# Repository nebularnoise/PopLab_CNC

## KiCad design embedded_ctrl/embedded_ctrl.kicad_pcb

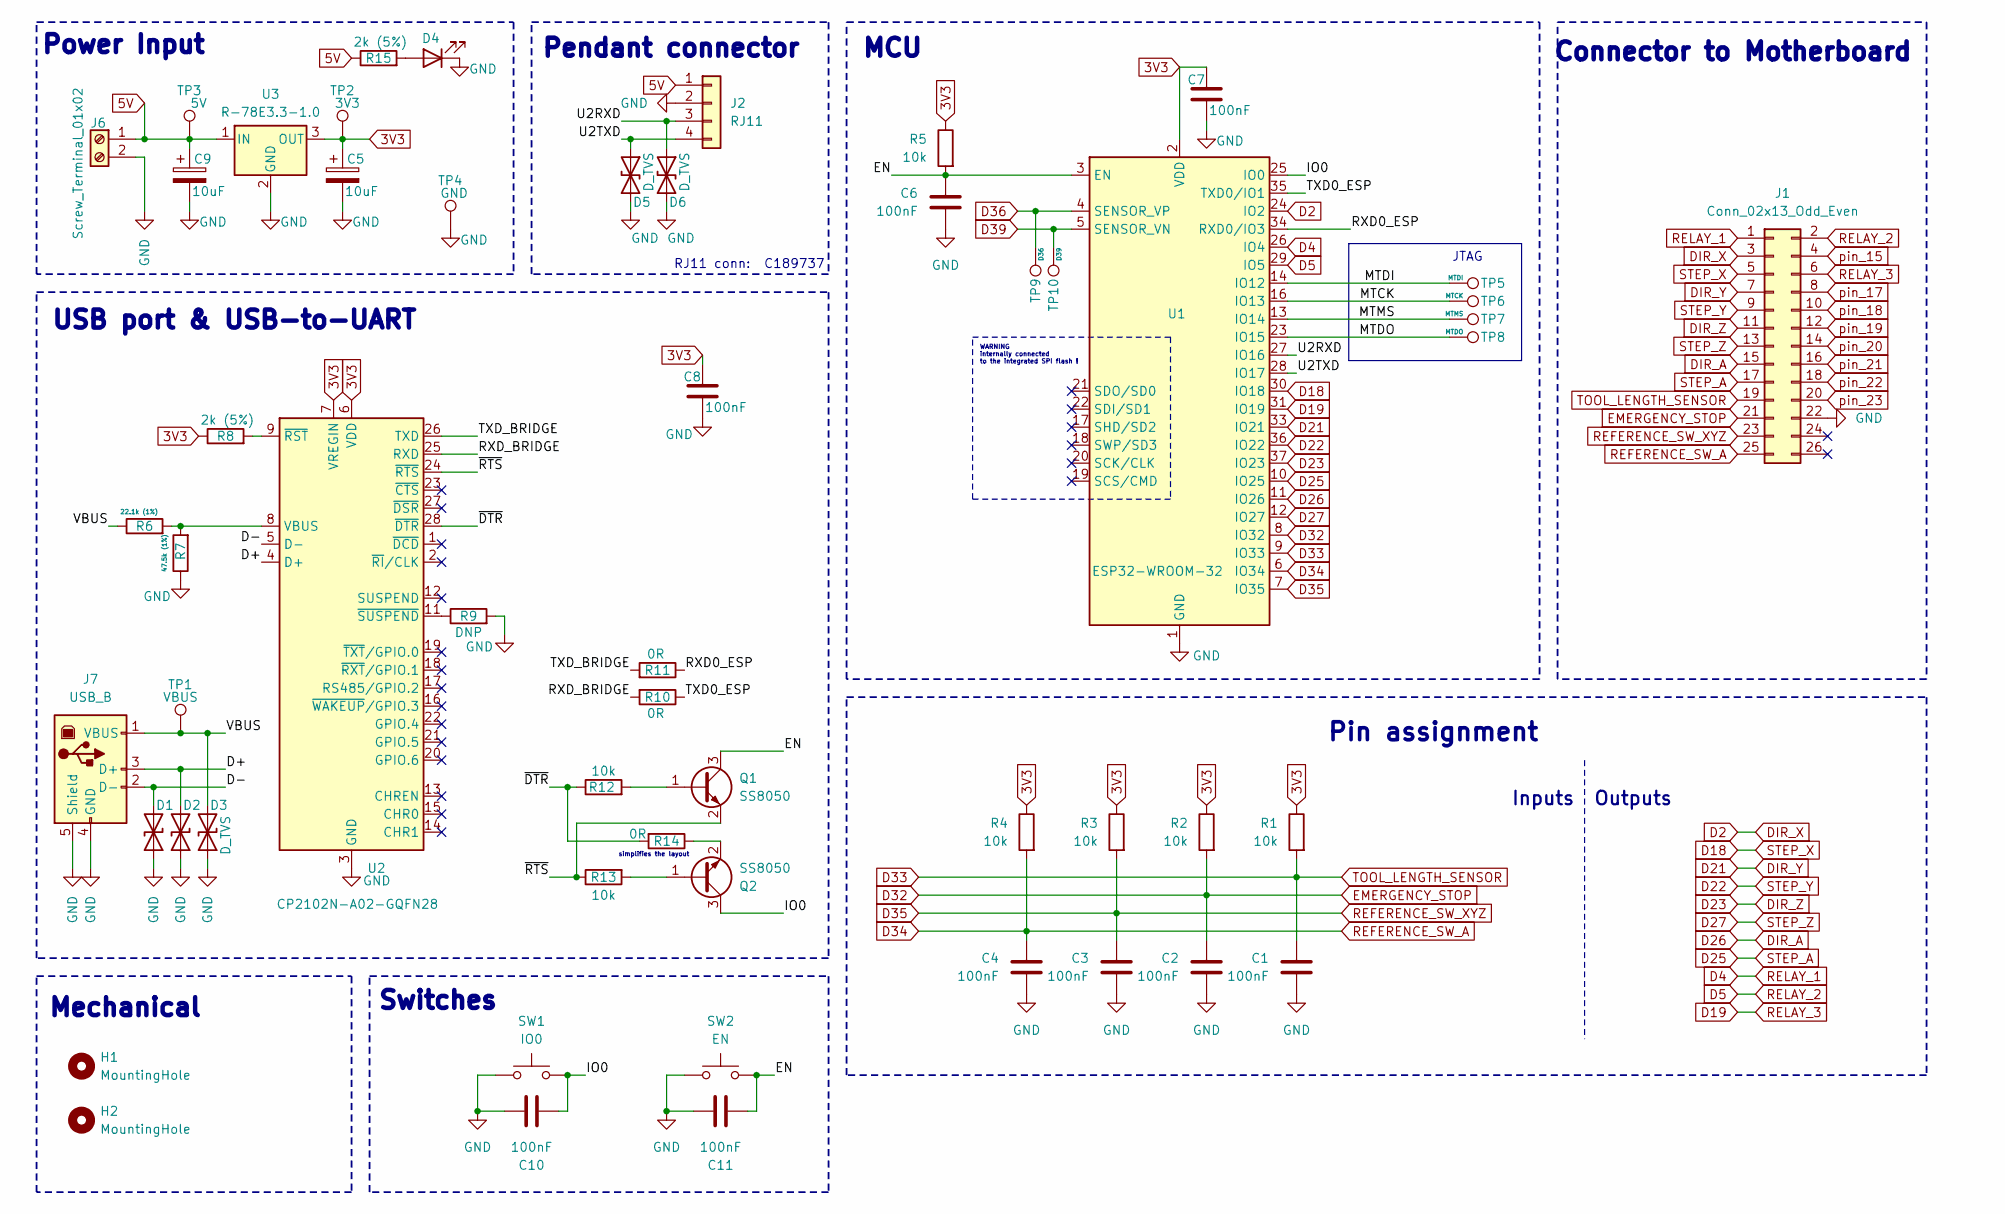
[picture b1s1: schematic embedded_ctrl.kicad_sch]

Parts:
C1, C2, C3, C4, C6, C7, C8, C10, C11: 100nF; C_0603_1608Metric; JLCPCB Part # C14663
C5, C9: 10uF; CP_Elec_5x5.4; JLCPCB Part # C72487
D1, D2, D3, D5, D6: D_TVS; D_0603_1608Metric; JLCPCB Part # C316054
D4: LED; D_0603_1608Metric; JLCPCB Part # C2286
H1, H2: MountingHole; MountingHole_3.2mm_M3
J1: Conn_02x13_Odd_Even; PinHeader_2x13_P2.54mm_Horizontal; JLCPCB Part # C2894993
J2: RJ11; RJ11_C189737
J6: Screw_Terminal_01x02; TerminalBlock_Phoenix_MKDS-1,5-2_1x02_P5.00mm_Horizontal; JLCPCB Part # C8465
J7: USB_B; USB_B_OST_USB-B1HSxx_Horizontal; JLCPCB Part # C720549
Q1, Q2: SS8050; SOT-23; JLCPCB Part # C2150
R1, R2, R3, R4, R5, R12, R13: 10k; R_0603_1608Metric; JLCPCB Part # C25804
R6: 22.1k (1%); R_0603_1608Metric; JLCPCB Part # C25961
R7: 47.5k (1%); R_0603_1608Metric; JLCPCB Part # C25961
R8, R15: 2k (5%); R_0603_1608Metric; JLCPCB Part # C22975
R9: DNP; R_0603_1608Metric
R10, R11, R14: 0R; R_0603_1608Metric; JLCPCB Part # C21189
SW1: IO0; SW_Push_1P1T_NO_Vertical_Wuerth_434133025816
SW2: EN; SW_Push_1P1T_NO_Vertical_Wuerth_434133025816
TP1: VBUS; TestPoint_THTPad_D1.0mm_Drill0.5mm
TP2: 3V3; TestPoint_THTPad_D1.0mm_Drill0.5mm
TP3: 5V; TestPoint_THTPad_D1.0mm_Drill0.5mm
TP4: GND; TestPoint_THTPad_D1.0mm_Drill0.5mm
TP5: MTDI; TestPoint_Pad_D1.0mm
TP6: MTCK; TestPoint_Pad_D1.0mm
TP7: MTMS; TestPoint_Pad_D1.0mm
TP8: MTDO; TestPoint_Pad_D1.0mm
TP9: D36; TestPoint_Pad_D1.0mm
TP10: D39; TestPoint_Pad_D1.0mm
U1: ESP32-WROOM-32
U2: CP2102N-A02-GQFN28; QFN-28-1EP_5x5mm_P0.5mm_EP3.35x3.35mm; JLCPCB Part # C964632
U3: R-78E3.3-1.0; Converter_DCDC_RECOM_R-78E-0.5_THT; JLCPCB Part # C18212316

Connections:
3V3: C5.1, C7.1, C8.1, R1.1, R2.1, R3.1, R4.1, R5.1, R8.1, TP2.1, U1.2 (VDD), U2.6 (VDD), U2.7 (VREGIN), U3.3 (OUT)
5V: C9.1, J2.1, J6.1, R15.1, TP3.1, U3.1 (IN)
/D+: D2.2 (A2), J7.3 (D+), U2.4 (D+)
/D-: D1.2 (A2), J7.2 (D-), U2.5 (D-)
/EN: C6.1, C11.1, Q1.3 (C), R5.2, SW2.2, U1.3 (EN)
/IO0: C10.1, Q2.3 (C), SW1.2, U1.25 (IO0)
/MTCK: TP6.1, U1.16 (IO13)
/MTDI: TP5.1, U1.14 (IO12)
/MTDO: TP8.1, U1.23 (IO15)
/MTMS: TP7.1, U1.13 (IO14)
/RXD0_ESP: R11.1, U1.34 (RXD0/IO3)
/RXD_BRIDGE: R10.2, U2.25 (RXD)
/TXD0_ESP: R10.1, U1.35 (TXD0/IO1)
/TXD_BRIDGE: R11.2, U2.26 (TXD)
/U2RXD: D6.1 (A1), J2.3, U1.27 (IO16)
/U2TXD: D5.1 (A1), J2.4, U1.28 (IO17)
/VBUS: D3.2 (A2), J7.1 (VBUS), R6.1, TP1.1
/~DTR: R12.1, R14.2, U2.28 (~DTR)
/~RTS: Q1.2 (E), R13.1, U2.24 (~RTS)
D2: J1.3, U1.24 (IO2)
D4: J1.1, U1.26 (IO4)
D5: J1.2, U1.29 (IO5)
D18: J1.5, U1.30 (IO18)
D19: J1.6, U1.31 (IO19)
D21: J1.7, U1.33 (IO21)
D22: J1.9, U1.36 (IO22)
D23: J1.11, U1.37 (IO23)
D25: J1.17, U1.10 (IO25)
D26: J1.15, U1.11 (IO26)
D27: J1.13, U1.12 (IO27)
D32: C2.1, J1.21, R2.2, U1.8 (IO32)
D33: C1.1, J1.19, R1.2, U1.9 (IO33)
D34: C4.1, J1.25, R4.2, U1.6 (IO34)
D35: C3.1, J1.23, R3.2, U1.7 (IO35)
D36: TP9.1, U1.4 (SENSOR_VP)
D39: TP10.1, U1.5 (SENSOR_VN)
GND: C1.2, C2.2, C3.2, C4.2, C5.2, C6.2, C7.2, C8.2, C9.2, C10.2, C11.2, D1.1 (A1), D2.1 (A1), D3.1 (A1), D4.1 (K), D5.2 (A2), D6.2 (A2), J1.22, J2.2, J6.2, J7.4 (GND), J7.5 (Shield), R7.1, R9.2, SW1.1, SW2.1, TP4.1, U1.1 (GND), U1.15 (GND), U1.38 (GND), U1.39 (GND), U2.3 (GND), U2.29 (GND), U3.2 (GND)
unnamed: D4.2 (A), R15.2
unnamed: Q1.1 (B), R12.2
unnamed: Q2.1 (B), R13.2
unnamed: Q2.2 (E), R14.1
unnamed: R6.2, R7.2, U2.8 (VBUS)
unnamed: R8.2, U2.9 (~RST)
unnamed: R9.1, U2.11 (~SUSPEND)
pin_15: J1.4
pin_17: J1.8
pin_18: J1.10
pin_19: J1.12
pin_20: J1.14
pin_21: J1.16
pin_22: J1.18
pin_23: J1.20

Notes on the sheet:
Outputs
JTAG
RJ11 conn: C189737
Power Input
Inputs
simplifies the layout
Mechanical
Connector to Motherboard
Switches
Pendant connector
Pin assignment
USB port & USB-to-UART
MCU
WARNING internally connected to the integrated SPI flash !

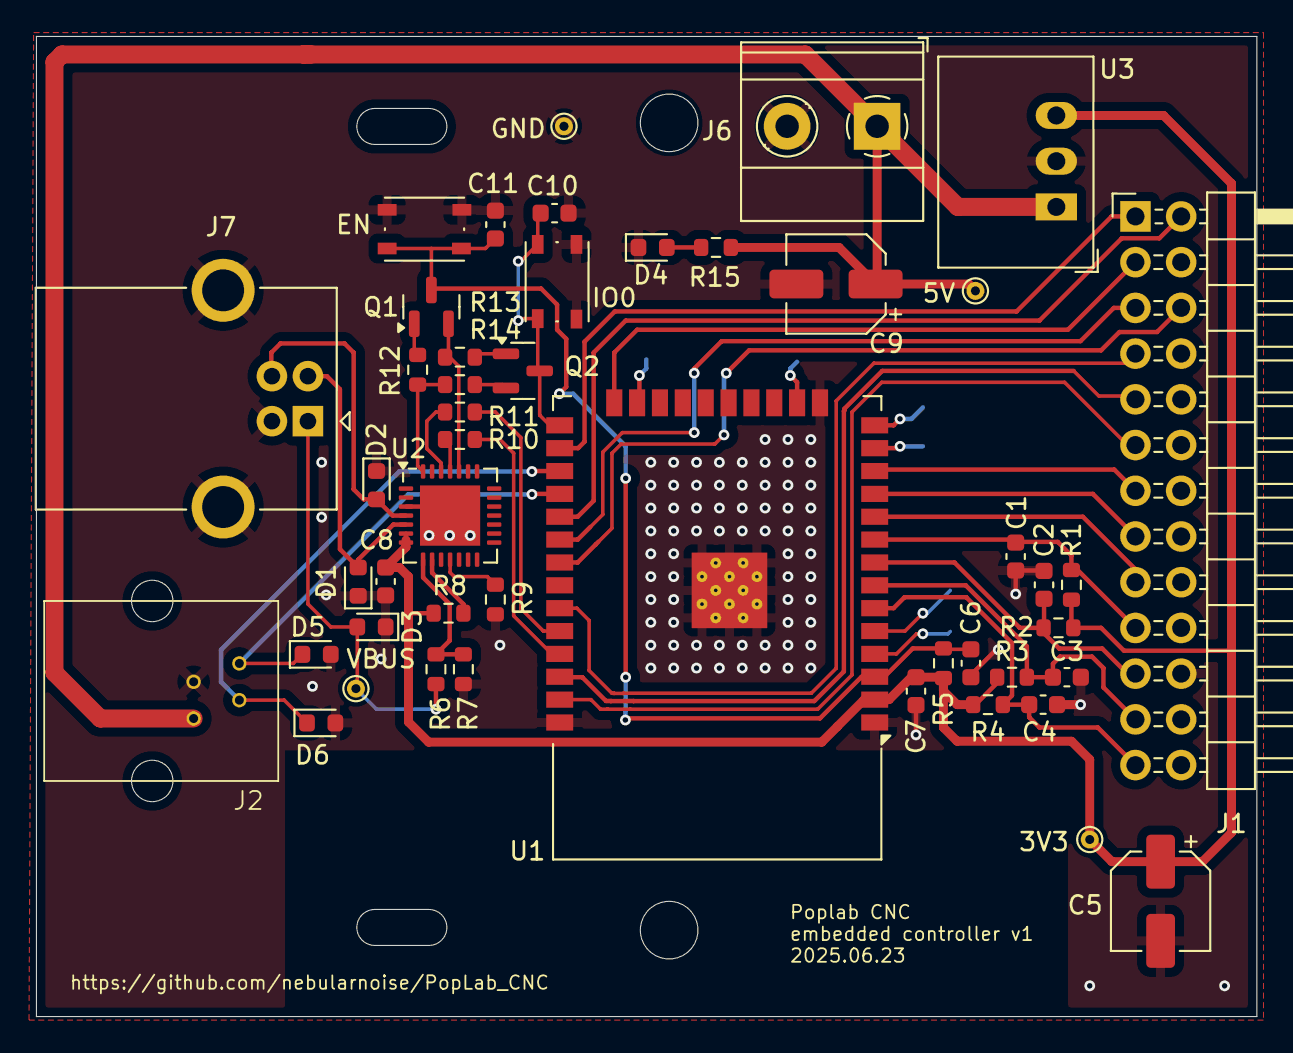
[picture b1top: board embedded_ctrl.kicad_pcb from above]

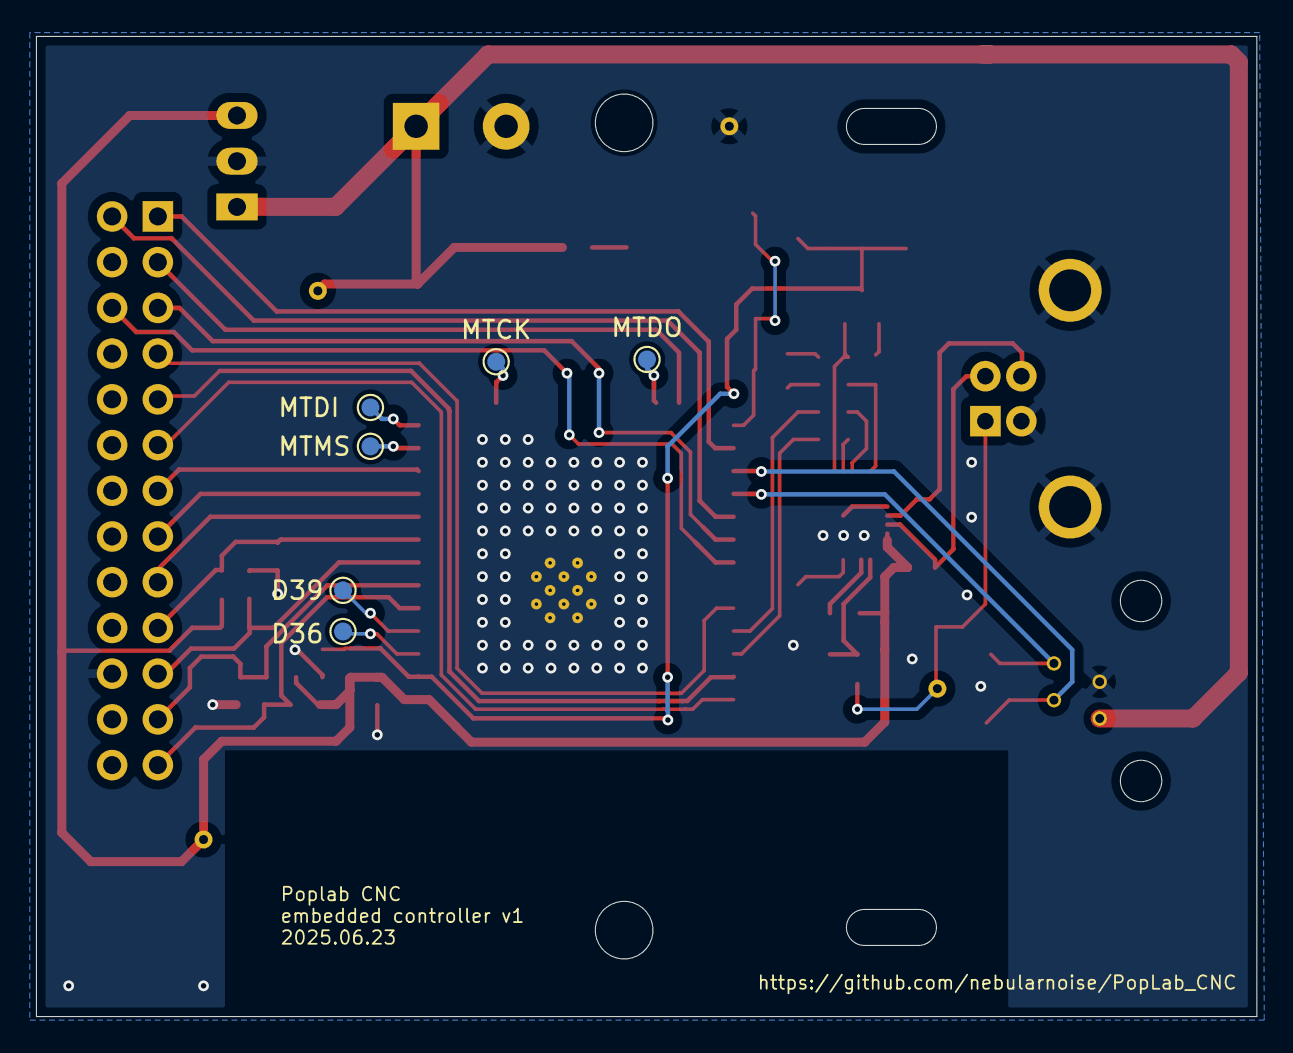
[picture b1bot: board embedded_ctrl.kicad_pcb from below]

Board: 2 copper layers, 67.8 x 54.5 mm, 55 parts (6 on the bottom side), 44 nets.

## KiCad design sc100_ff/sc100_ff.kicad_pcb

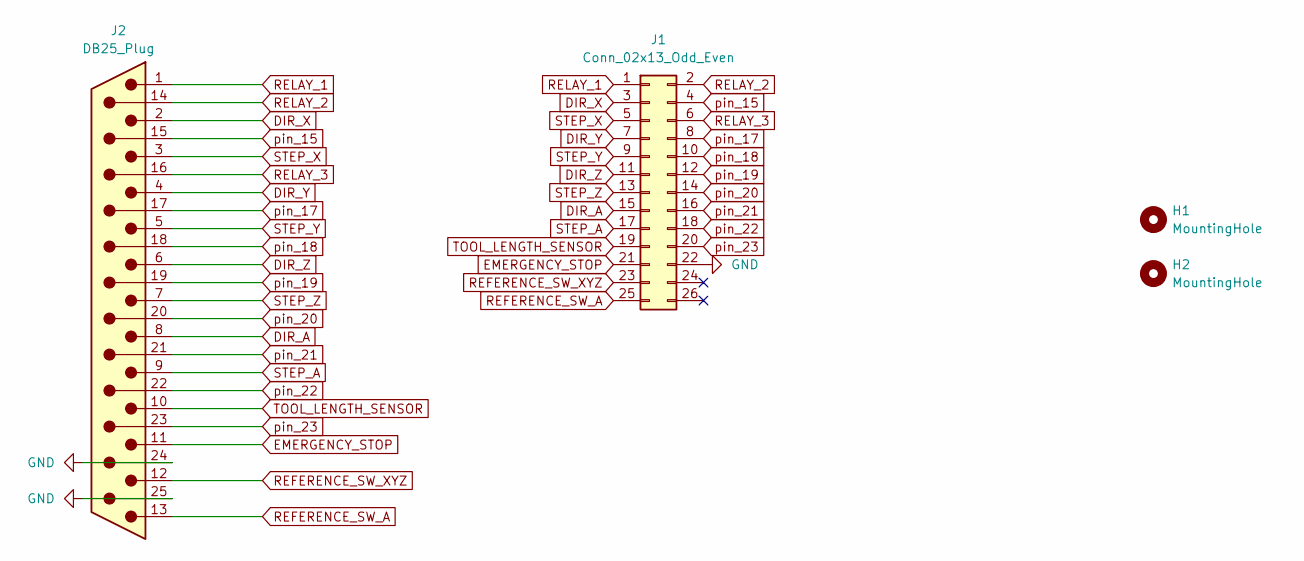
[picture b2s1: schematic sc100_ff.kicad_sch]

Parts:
H1, H2: MountingHole; MountingHole_3.2mm_M3
J1: Conn_02x13_Odd_Even; PinHeader_2x13_P2.54mm_Horizontal
J2: DB25_Plug; DSUB-25_Male_Horizontal_P2.77x2.54mm_EdgePinOffset9.40mm

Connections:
DIR_A: J1.15, J2.8
DIR_X: J1.3, J2.2
DIR_Y: J1.7, J2.4
DIR_Z: J1.11, J2.6
EMERGENCY_STOP: J1.21, J2.11
GND: J1.22, J2.24, J2.25
REFERENCE_SW_A: J1.25, J2.13
REFERENCE_SW_XYZ: J1.23, J2.12
RELAY_1: J1.1, J2.1
RELAY_2: J1.2, J2.14
RELAY_3: J1.6, J2.16
STEP_A: J1.17, J2.9
STEP_X: J1.5, J2.3
STEP_Y: J1.9, J2.5
STEP_Z: J1.13, J2.7
TOOL_LENGTH_SENSOR: J1.19, J2.10
pin_15: J1.4, J2.15
pin_17: J1.8, J2.17
pin_18: J1.10, J2.18
pin_19: J1.12, J2.19
pin_20: J1.14, J2.20
pin_21: J1.16, J2.21
pin_22: J1.18, J2.22
pin_23: J1.20, J2.23

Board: 2 copper layers, 4 parts (0 on the bottom side), 24 nets, no tracks yet.

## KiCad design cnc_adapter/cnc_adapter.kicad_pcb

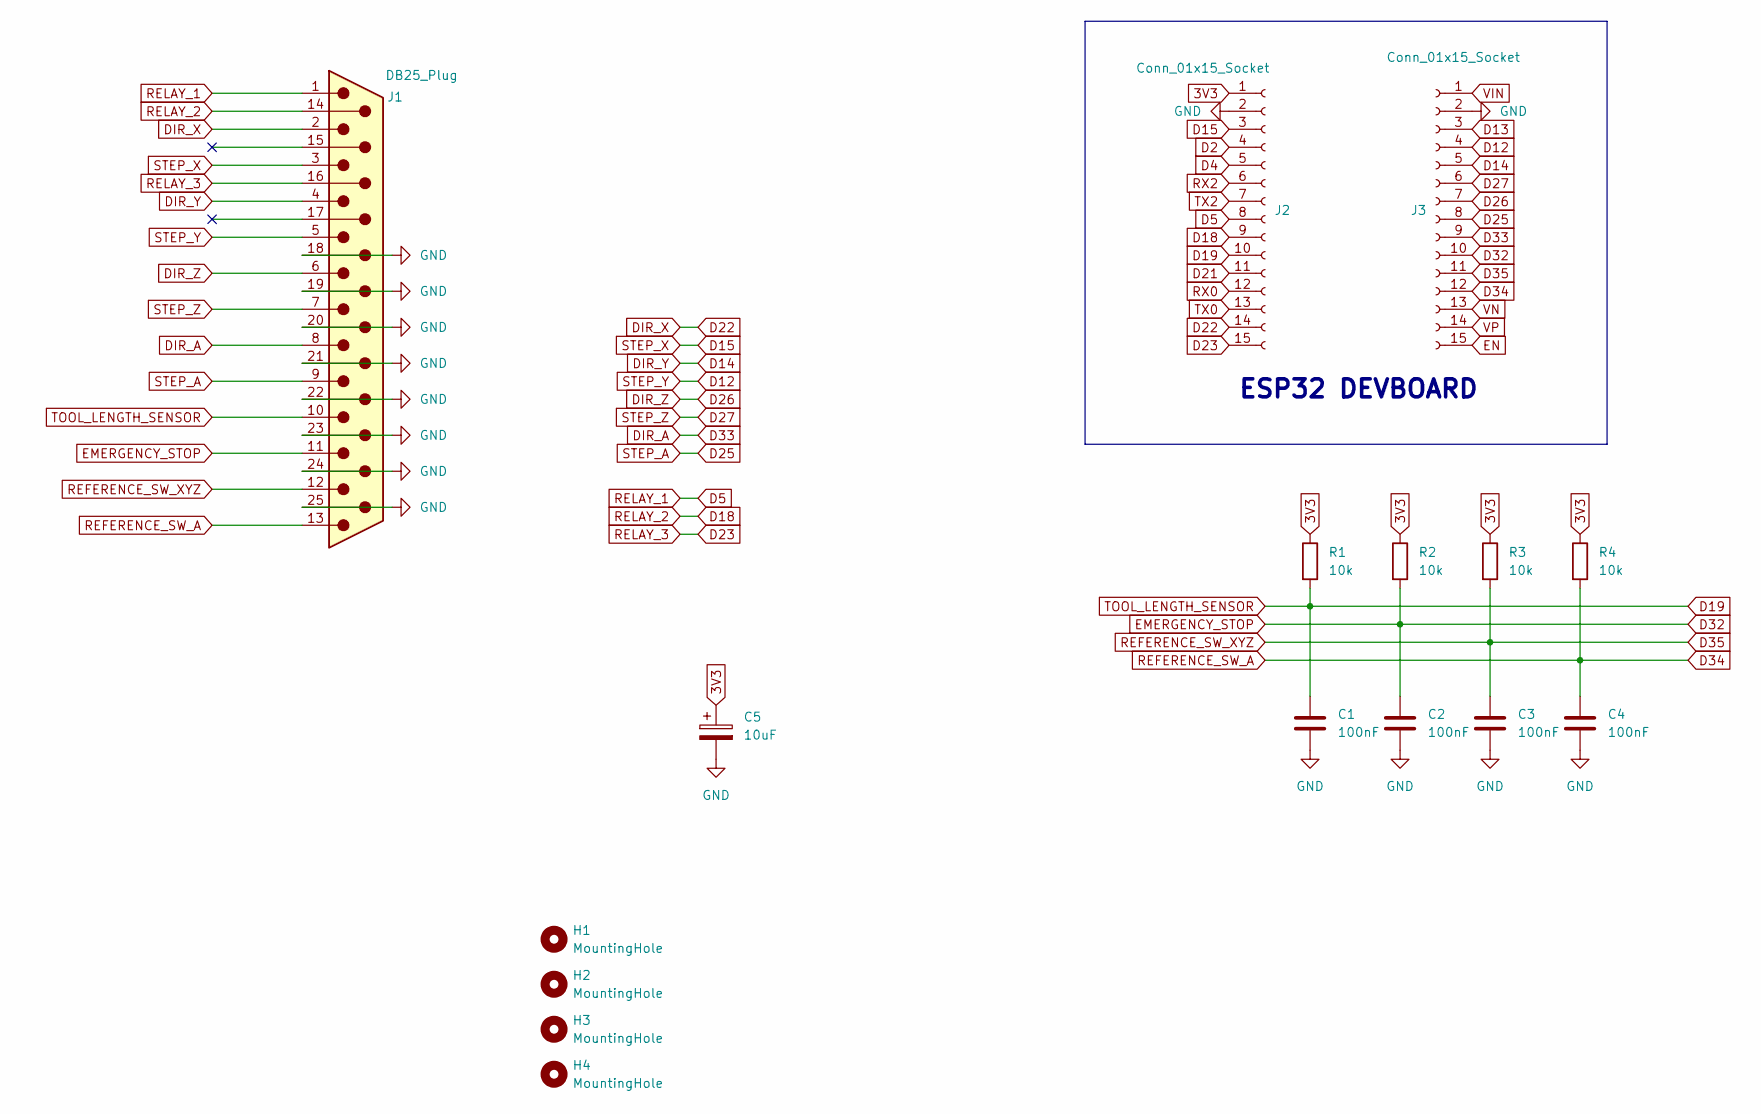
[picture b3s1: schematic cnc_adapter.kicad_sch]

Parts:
C1, C2, C3, C4: 100nF; C_0603_1608Metric
C5: 10uF; CP_Elec_5x5.8
H1, H2, H3, H4: MountingHole; MountingHole_2.7mm_M2.5
J1: DB25_Plug; DSUB-25_Female_EdgeMount_P2.77mm
J2, J3: Conn_01x15_Socket; PinSocket_1x15_P2.54mm_Vertical
R1, R2, R3, R4: 10k; R_0603_1608Metric

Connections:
3V3: C5.1, J2.1, R1.1, R2.1, R3.1, R4.1
D2: J2.4
D4: J2.5
D5: J1.1, J2.8
D12: J1.5, J3.4
D13: J3.3
D14: J1.4, J3.5
D15: J1.3, J2.3
D18: J1.14, J2.9
D19: C1.1, J1.10, J2.10, R1.2
D21: J2.11
D22: J1.2, J2.14
D23: J1.16, J2.15
D25: J1.9, J3.8
D26: J1.6, J3.7
D27: J1.7, J3.6
D32: C2.1, J1.11, J3.10, R2.2
D33: J1.8, J3.9
D34: C4.1, J1.13, J3.12, R4.2
D35: C3.1, J1.12, J3.11, R3.2
EN: J3.15
GND: C1.2, C2.2, C3.2, C4.2, C5.2, J1.18, J1.19, J1.20, J1.21, J1.22, J1.23, J1.24, J1.25, J2.2, J3.2
RX0: J2.12
RX2: J2.6
TX0: J2.13
TX2: J2.7
VIN: J3.1
VN: J3.13
VP: J3.14

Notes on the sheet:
ESP32 DEVBOARD

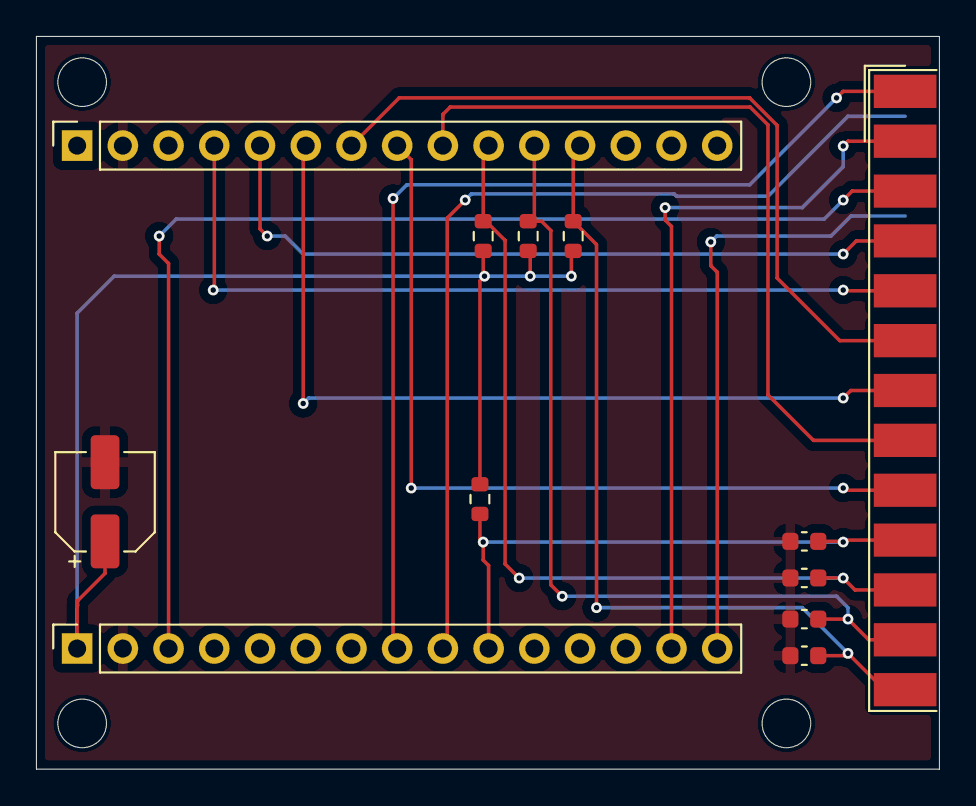
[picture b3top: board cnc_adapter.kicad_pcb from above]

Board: 2 copper layers, 50.2 x 40.7 mm, 16 parts (0 on the bottom side), 17 nets.

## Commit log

2025-01-15 :construction: first draft passive adapter esp32 <-> parallel port
2025-06-04 Finish draft
2025-06-04 Add version silkscreen
2025-06-20 :construction: first draft sc100ff clone
2025-06-20 :construction: first draft embedded controller
    wip
2025-06-21 more work on embedded ctrlr
    same-o
2025-06-21 add rj11 connectors for pendants
2025-06-21 improve pcb layout
2025-06-22 same
2025-06-22 Reassign pins to free up JTAG pins, just in case
2025-06-22 Don't use UART1 - its pins are already in use for the SPI flash
2025-06-23 Expose D36 and D39. Add buttons for EN and IO0,bodge wire passthrus, and version text
2025-06-30 add tvs diodes to uart connector
2025-06-30 trace and ignore gerbers
